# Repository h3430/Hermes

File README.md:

# Radio gateway

Work in progres...

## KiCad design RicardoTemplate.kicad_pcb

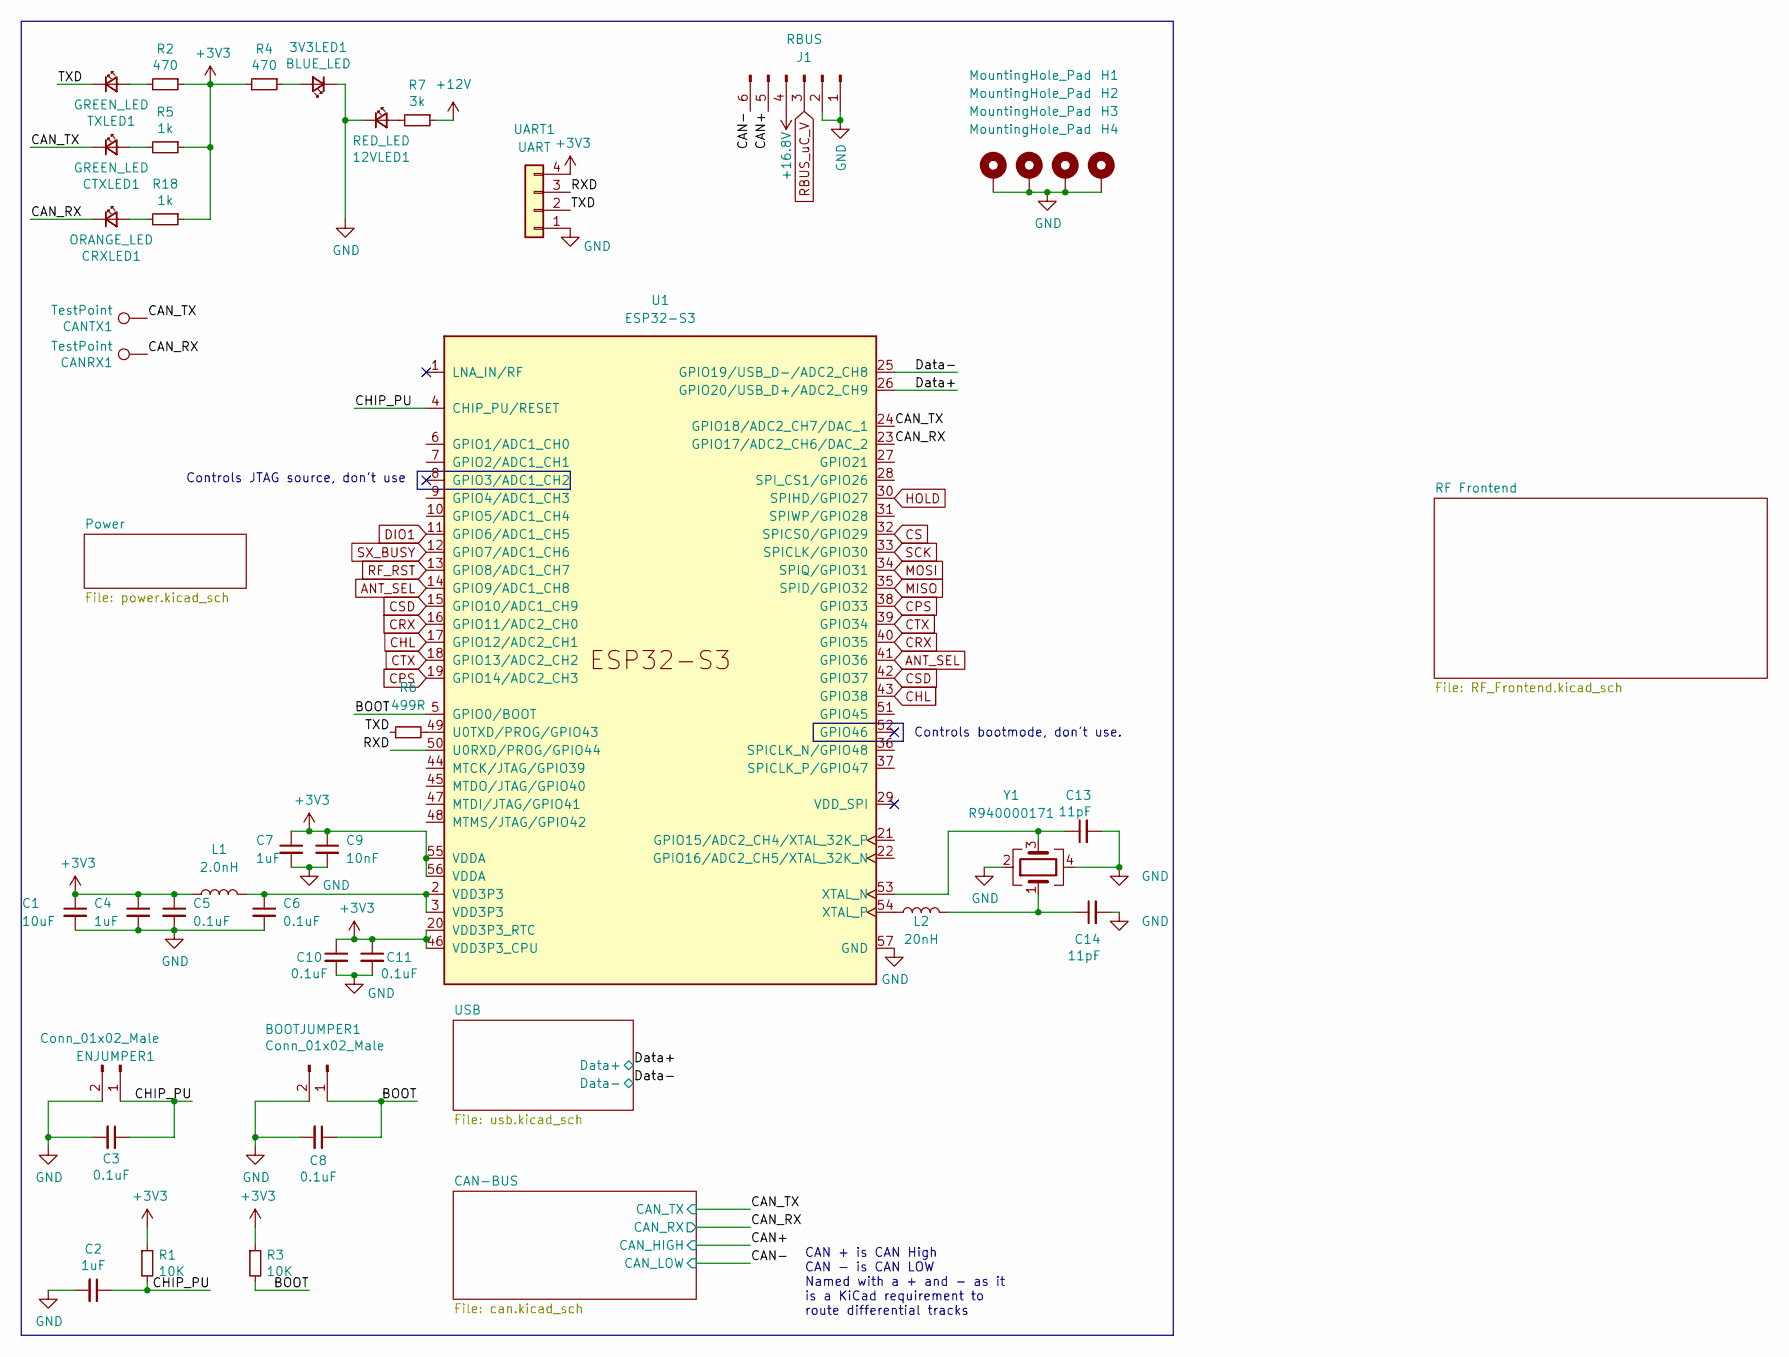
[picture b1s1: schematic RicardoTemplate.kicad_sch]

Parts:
3V3LED1: BLUE_LED; R_0402_1005Metric
12VLED1: RED_LED; R_0402_1005Metric
BOOTJUMPER1: Conn_01x02_Male; PinHeader_1x02_P2.54mm_Vertical
C1: 10uF; C_0402_1005Metric
C2, C4, C7: 1uF; C_0402_1005Metric
C3, C5, C6, C8, C10, C11: 0.1uF; C_0402_1005Metric
C9: 10nF; C_0402_1005Metric
C13, C14: 11pF; C_0402_1005Metric
CANRX1: TestPoint; TestPoint_Pad_D1.0mm
CANTX1: TestPoint; TestPoint_Pad_D1.0mm
CRXLED1: ORANGE_LED; R_0402_1005Metric
CTXLED1: GREEN_LED; R_0402_1005Metric
ENJUMPER1: Conn_01x02_Male; PinHeader_1x02_P2.54mm_Vertical
H1, H2, H3, H4: MountingHole_Pad; MountingHole_3.2mm_M3_DIN965_Pad
J1: RBUS; Molex_Mini-Fit_Jr_5566-06A_2x03_P4.20mm_Vertical
L1: 2.0nH; L_0402_1005Metric
L2: 20nH; L_0402_1005Metric
R1, R3: 10K; R_0402_1005Metric
R2, R4: 470; R_0402_1005Metric
R5, R18: 1k; R_0402_1005Metric
R6: 499R; R_0402_1005Metric
R7: 3k; R_0402_1005Metric
TXLED1: GREEN_LED; R_0402_1005Metric
U1: ESP32-S3; QFN40P700X700X90-57N
UART1: UART; PinHeader_1x04_P2.54mm_Vertical
Y1: R940000171; Crystal_SMD_2016-4Pin_2.0x1.6mm

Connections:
+3V3: C1.1, C4.1, C5.1, C7.1, C9.1, C10.1, C11.1, L1.1, R1.1, R2.1, R3.1, R4.2, R5.1, R18.1, U1.20 (VDD3P3_RTC), U1.46 (VDD3P3_CPU), U1.55 (VDDA), U1.56 (VDDA), UART1.4; also elsewhere on the board
+12V: R7.1
+16.8V: J1.4
/BOOT: BOOTJUMPER1.1, C8.1, R3.2, U1.5 (GPIO0/BOOT)
/CAN+: J1.5; also elsewhere on the board
/CAN-: J1.6; also elsewhere on the board
/CAN_RX: CANRX1.1, CRXLED1.1 (K), U1.23 (GPIO17/ADC2_CH6/DAC_2); also elsewhere on the board
/CAN_TX: CANTX1.1, CTXLED1.1 (K), U1.24 (GPIO18/ADC2_CH7/DAC_1); also elsewhere on the board
/CHIP_PU: C2.1, C3.1, ENJUMPER1.1, R1.2, U1.4 (CHIP_PU/RESET)
/Data+: U1.26 (GPIO20/USB_D+/ADC2_CH9); also elsewhere on the board
/Data-: U1.25 (GPIO19/USB_D-/ADC2_CH8); also elsewhere on the board
/RXD: U1.50 (U0RXD/PROG/GPIO44), UART1.3
/TXD: R6.1, TXLED1.1 (K), UART1.2
ANT_SEL: U1.14 (GPIO9/ADC1_CH8), U1.41 (GPIO36); also elsewhere on the board
CHL: U1.17 (GPIO12/ADC2_CH1), U1.43 (GPIO38); also elsewhere on the board
CPS: U1.19 (GPIO14/ADC2_CH3), U1.38 (GPIO33); also elsewhere on the board
CRX: U1.16 (GPIO11/ADC2_CH0), U1.40 (GPIO35); also elsewhere on the board
CS: U1.32 (SPICS0/GPIO29); also elsewhere on the board
CSD: U1.15 (GPIO10/ADC1_CH9), U1.42 (GPIO37); also elsewhere on the board
CTX: U1.18 (GPIO13/ADC2_CH2), U1.39 (GPIO34); also elsewhere on the board
DIO1: U1.11 (GPIO6/ADC1_CH5); also elsewhere on the board
GND: 3V3LED1.1 (K), 12VLED1.1 (K), BOOTJUMPER1.2, C1.2, C2.2, C3.2, C4.2, C5.2, C6.2, C7.2, C8.2, C9.2, C10.2, C11.2, C13.2, C14.2, ENJUMPER1.2, H1.1, H2.1, H3.1, H4.1, J1.1, J1.2, U1.57 (GND), UART1.1, Y1.2, Y1.4; also elsewhere on the board
HOLD: U1.30 (SPIHD/GPIO27)
MISO: U1.35 (SPID/GPIO32); also elsewhere on the board
MOSI: U1.34 (SPIQ/GPIO31); also elsewhere on the board
unnamed: 3V3LED1.2 (A), R4.1
unnamed: 12VLED1.2 (A), R7.2
unnamed: C6.1, L1.2, U1.2 (VDD3P3), U1.3 (VDD3P3)
unnamed: C14.1, L2.2, Y1.1
unnamed: CRXLED1.2 (A), R18.2
unnamed: CTXLED1.2 (A), R5.2
unnamed: R2.2, TXLED1.2 (A)
unnamed: R6.2, U1.49 (U0TXD/PROG/GPIO43)
unnamed: C13.1, U1.53 (XTAL_N), Y1.3
unnamed: L2.1, U1.54 (XTAL_P)
RBUS_uC_V: J1.3; also elsewhere on the board
RF_RST: U1.13 (GPIO8/ADC1_CH7); also elsewhere on the board
SCK: U1.33 (SPICLK/GPIO30); also elsewhere on the board
SX_BUSY: U1.12 (GPIO7/ADC1_CH6); also elsewhere on the board

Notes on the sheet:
Controls bootmode, don't use.
CAN + is CAN High CAN - is CAN LOW Named with a + and - as it is a KiCad requirement to route differential tracks
Controls JTAG source, don't use

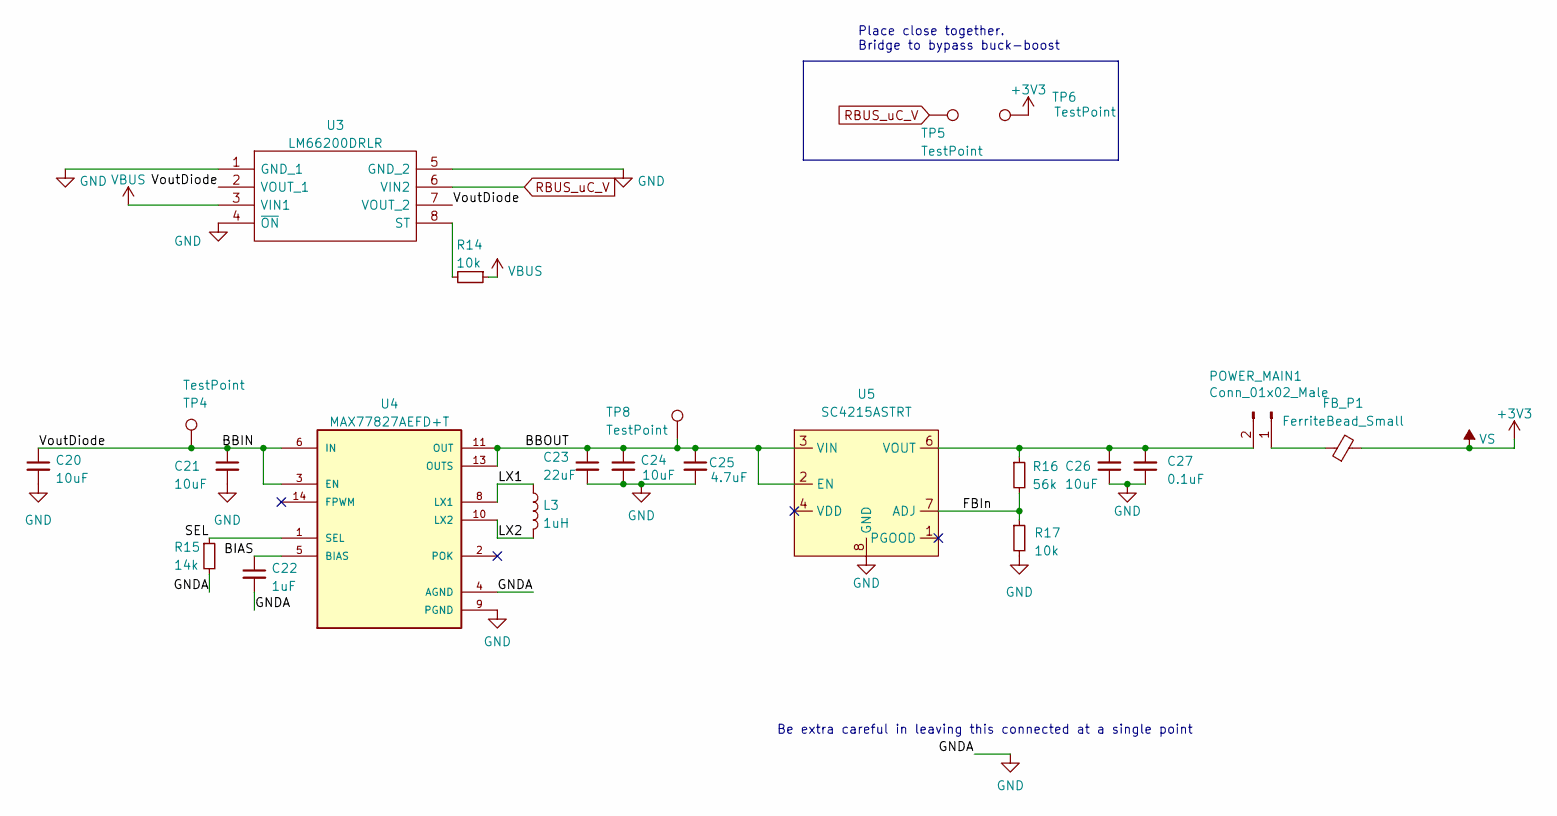
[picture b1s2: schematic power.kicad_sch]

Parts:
C20, C24, C26: 10uF; C_0402_1005Metric
C21: 10uF; C_0603_1608Metric
C22: 1uF; C_0402_1005Metric
C23: 22uF; C_0603_1608Metric
C25: 4.7uF; C_0402_1005Metric
C27: 0.1uF; C_0402_1005Metric
FB_P1: FerriteBead_Small; L_0603_1608Metric
L3: 1uH; L_0805_2012Metric
POWER_MAIN1: Conn_01x02_Male; PinHeader_1x02_P2.54mm_Vertical
R14, R17: 10k; R_0402_1005Metric
R15: 14k; R_0402_1005Metric
R16: 56k; R_0402_1005Metric
TP4, TP5, TP6, TP8: TestPoint; TestPoint_Pad_D1.5mm
U3: LM66200DRLR; SOTFL50P160X60-8N; Manufacturer_Part_Number LM66200DRLR; Mouser Part Number 595-LM66200DRLR
U4: MAX77827AEFD+T; CONV_MAX77827AEFD+T; PARTREV B
U5: SC4215ASTRT; SOIC127P599X175-9N

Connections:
+3V3: FB_P1.2, TP6.1; also elsewhere on the board
/Power/BBIN: C20.1, C21.1, TP4.1, U3.2 (VOUT_1), U3.7 (VOUT_2), U4.3 (EN), U4.6 (IN)
/Power/BBOUT: C23.1, C24.1, C25.1, TP8.1, U4.11 (OUT), U4.13 (OUTS), U5.2 (EN), U5.3 (VIN)
/Power/BIAS: C22.1, U4.5 (BIAS)
/Power/FBIn: R16.2, R17.1, U5.7 (ADJ)
/Power/LX1: L3.1, U4.8 (LX1)
/Power/LX2: L3.2, U4.10 (LX2)
/Power/SEL: R15.1, U4.1 (SEL)
GND: C20.2, C21.2, C22.2, C23.2, C24.2, C25.2, C26.1, C27.1, R15.2, R17.2, U3.1 (GND_1), U3.4 (~ON), U3.5 (GND_2), U4.4 (AGND), U4.9 (PGND), U5.8 (GND), U5.9 (GND); also elsewhere on the board
unnamed: FB_P1.1, POWER_MAIN1.1
unnamed: C26.2, C27.2, POWER_MAIN1.2, R16.1, U5.6 (VOUT)
unnamed: R14.2, U3.8 (ST)
RBUS_uC_V: TP5.1, U3.6 (VIN2); also elsewhere on the board
VBUS: R14.1, U3.3 (VIN1); also elsewhere on the board

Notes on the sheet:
Place close together. Bridge to bypass buck-boost
Be extra careful in leaving this connected at a single point

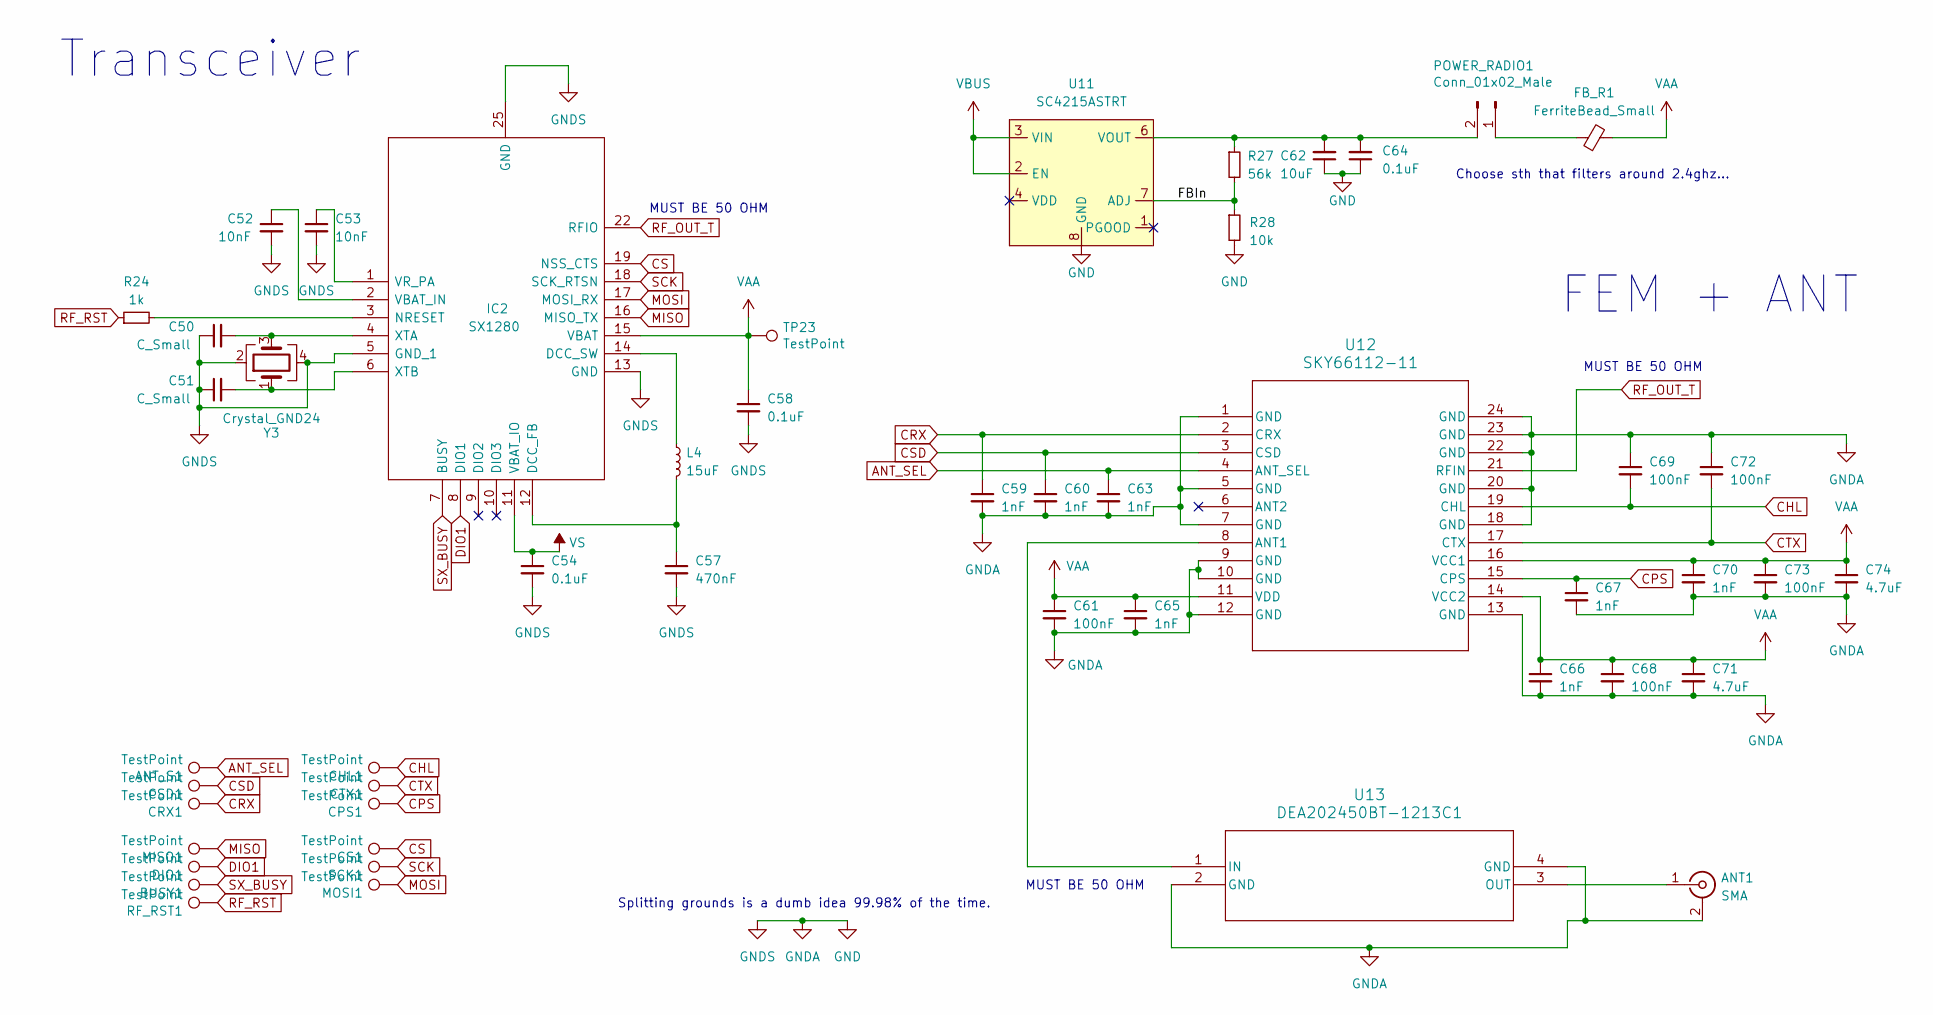
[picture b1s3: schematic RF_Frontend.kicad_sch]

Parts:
ANT1: SMA; SMA_Amphenol_901-144_Vertical
ANT_S1: TestPoint; TestPoint_Pad_D1.0mm
BUSY1: TestPoint; TestPoint_Pad_D1.0mm
C50, C51: C_Small; C_0402_1005Metric
C52, C53: 10nF; C_0402_1005Metric
C54, C58, C64: 0.1uF; C_0402_1005Metric
C57: 470nF; C_0402_1005Metric
C59, C60, C63, C65, C66, C67, C70: 1nF; C_0402_1005Metric
C61, C68, C69, C72, C73: 100nF; C_0402_1005Metric
C62: 10uF; C_0402_1005Metric
C71, C74: 4.7uF; C_0603_1608Metric
CHL1: TestPoint; TestPoint_Pad_D1.0mm
CPS1: TestPoint; TestPoint_Pad_D1.0mm
CRX1: TestPoint; TestPoint_Pad_D1.0mm
CS1: TestPoint; TestPoint_Pad_D1.0mm
CSD1: TestPoint; TestPoint_Pad_D1.0mm
CTX1: TestPoint; TestPoint_Pad_D1.0mm
DIO1: TestPoint; TestPoint_Pad_D1.0mm
FB_R1: FerriteBead_Small; L_0603_1608Metric
IC2: SX1280; QFN50P400X400X95-24N; Manufacturer_Part_Number SX1280IMLTRT; Mouser Part Number 947-SX1280IMLTRT
L4: 15uF; C_0603_1608Metric
MISO1: TestPoint; TestPoint_Pad_D1.0mm
MOSI1: TestPoint; TestPoint_Pad_D1.0mm
POWER_RADIO1: Conn_01x02_Male; PinHeader_1x02_P2.54mm_Vertical
R24: 1k; R_0402_1005Metric
R27: 56k; R_0402_1005Metric
R28: 10k; R_0402_1005Metric
RF_RST1: TestPoint; TestPoint_Pad_D1.0mm
SCK1: TestPoint; TestPoint_Pad_D1.0mm
TP23: TestPoint; TestPoint_Pad_D1.0mm
U11: SC4215ASTRT; SOIC127P599X175-9N
U12: SKY66112-11; SKY66112-11_SKY
U13: DEA202450BT-1213C1; DEA-4_2P0X1P25
Y3: Crystal_GND24; Crystal_SMD_2016-4Pin_2.0x1.6mm

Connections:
+3V3: C54.1, IC2.11 (VBAT_IO); also elsewhere on the board
/RF Frontend/FBIn: R27.2, R28.1, U11.7 (ADJ)
ANT_SEL: ANT_S1.1, C63.1, U12.4 (ANT_SEL); also elsewhere on the board
CHL: C69.2, CHL1.1, U12.19 (CHL); also elsewhere on the board
CPS: C67.1, CPS1.1, U12.15 (CPS); also elsewhere on the board
CRX: C59.1, CRX1.1, U12.2 (CRX); also elsewhere on the board
CS: CS1.1, IC2.19 (NSS_CTS); also elsewhere on the board
CSD: C60.1, CSD1.1, U12.3 (CSD); also elsewhere on the board
CTX: C72.2, CTX1.1, U12.17 (CTX); also elsewhere on the board
DIO1: DIO1.1, IC2.8 (DIO1); also elsewhere on the board
GND: ANT1.2 (Ext), C50.1, C51.1, C52.2, C53.2, C54.2, C57.2, C58.2, C59.2, C60.2, C61.2, C62.1, C63.2, C64.1, C65.2, C66.2, C67.2, C68.2, C69.1, C70.2, C71.2, C72.1, C73.2, C74.2, IC2.5 (GND_1), IC2.13 (GND), IC2.20 (GND), IC2.21 (GND), IC2.23 (GND), IC2.24 (GND), IC2.25 (GND), R28.2, U11.8 (GND), U11.9 (GND), U12.1 (GND), U12.5 (GND), U12.7 (GND), U12.9 (GND), U12.10 (GND), U12.12 (GND), U12.13 (GND), U12.18 (GND), U12.20 (GND), U12.22 (GND), U12.23 (GND), U12.24 (GND), U13.2 (GND), U13.4 (GND), Y3.2, Y3.4; also elsewhere on the board
MISO: IC2.16 (MISO_TX), MISO1.1; also elsewhere on the board
MOSI: IC2.17 (MOSI_RX), MOSI1.1; also elsewhere on the board
unnamed: ANT1.1 (In), U13.3 (OUT)
unnamed: C57.1, IC2.12 (DCC_FB), L4.2
unnamed: IC2.14 (DCC_SW), L4.1
unnamed: IC2.3 (NRESET), R24.2
unnamed: C52.1, IC2.2 (VBAT_IN)
unnamed: C53.1, IC2.1 (VR_PA)
unnamed: C50.2, IC2.4 (XTA), Y3.3
unnamed: C51.2, IC2.6 (XTB), Y3.1
unnamed: FB_R1.1, POWER_RADIO1.1
unnamed: C62.2, C64.2, POWER_RADIO1.2, R27.1, U11.6 (VOUT)
unnamed: U12.8 (ANT1), U13.1 (IN)
RF_OUT_T: IC2.22 (RFIO), U12.21 (RFIN)
RF_RST: R24.1, RF_RST1.1; also elsewhere on the board
SCK: IC2.18 (SCK_RTSN), SCK1.1; also elsewhere on the board
SX_BUSY: BUSY1.1, IC2.7 (BUSY); also elsewhere on the board
VAA: C58.1, C61.1, C65.1, C66.1, C68.1, C70.1, C71.1, C73.1, C74.1, FB_R1.2, IC2.15 (VBAT), TP23.1, U12.11 (VDD), U12.14 (VCC2), U12.16 (VCC1)
VBUS: U11.2 (EN), U11.3 (VIN); also elsewhere on the board

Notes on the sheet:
FEM + ANT
MUST BE 50 OHM
Transceiver
Choose sth that filters around 2.4ghz...
Splitting grounds is a dumb idea 99.98% of the time.

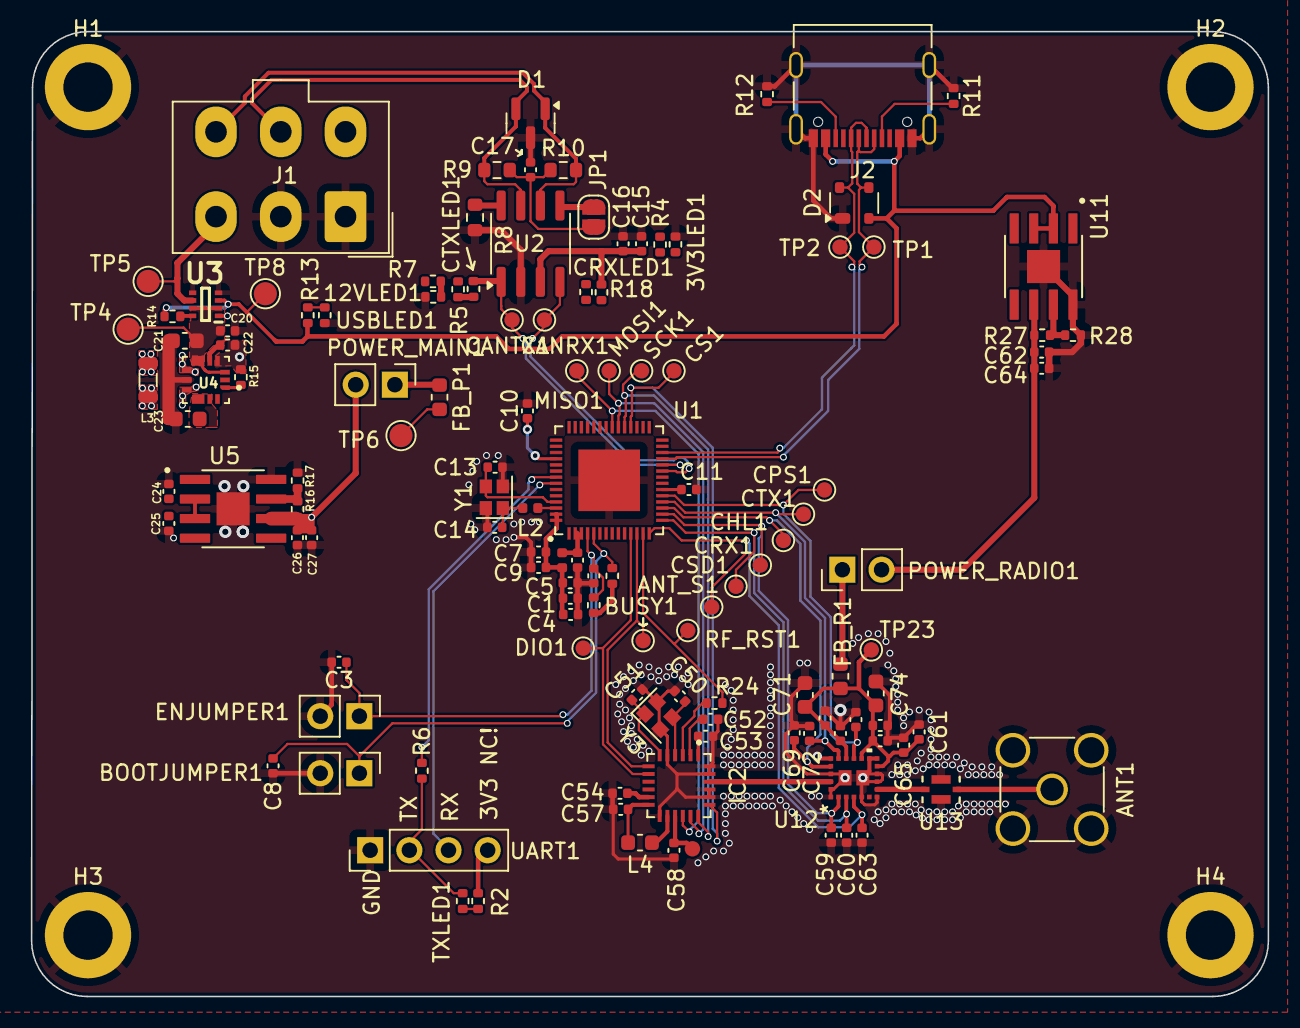
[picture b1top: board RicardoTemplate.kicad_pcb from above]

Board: 4 copper layers, 80.2 x 62.6 mm, 128 parts (0 on the bottom side), 67 nets.

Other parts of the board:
C15: 100nF; C_0402_1005Metric
C16: 10uF; C_0402_1005Metric
C17: 47nF; C_0402_1005Metric
D1: SM712_SOT23; SOT-23
D2: SP0503BAHT; SOT-143
J2: USB_C_Receptacle_USB2.0; USB_C_Receptacle_Palconn_UTC16-G
JP1: TermJP; SolderJumper-2_P1.3mm_Open_RoundedPad1.0x1.5mm
R8: 0; R_0603_1608Metric
R9, R10: 60; R_0603_1608Metric
R11, R12, R13: 5.1k; R_0402_1005Metric
TP1, TP2: TestPoint; TestPoint_Pad_D1.0mm
U2: SN65HVD230; SOIC-8_3.9x4.9mm_P1.27mm
USBLED1: WHITE_LED; R_0402_1005Metric

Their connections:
+3V3: C15.1, C16.1, U2.3 (VCC); also elsewhere on the board
/CAN+: D1.2 (A2), R9.1, U2.7 (CANH); also elsewhere on the board
/CAN-: D1.1 (A1), R10.2, U2.6 (CANL); also elsewhere on the board
/CAN-BUS/Vref: JP1.1 (A), U2.5 (Vref)
/CAN_RX: U2.4 (R); also elsewhere on the board
/CAN_TX: U2.1 (D); also elsewhere on the board
/Data+: D2.4 (K), J2.A6 (D+), J2.B6 (D+), TP2.1; also elsewhere on the board
/Data-: D2.3 (K), J2.A7 (D-), J2.B7 (D-), TP1.1; also elsewhere on the board
GND: C15.2, C16.2, C17.2, D1.3 (common), D2.1 (A), J2.A1 (GND), J2.A12 (GND), J2.B1 (GND), J2.B12 (GND), J2.S1 (SHIELD), R8.2, R11.2, R12.1, U2.2 (GND), USBLED1.1 (K); also elsewhere on the board
unnamed: J2.A5 (CC1), R11.1
unnamed: J2.B5 (CC2), R12.2
unnamed: C17.1, JP1.2 (B), R9.2, R10.1
unnamed: R8.1, U2.8 (Rs)
unnamed: R13.2, USBLED1.2 (A)
VBUS: D2.2 (K), J2.A4 (VBUS), J2.A9 (VBUS), J2.B4 (VBUS), J2.B9 (VBUS), R13.1; also elsewhere on the board

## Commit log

2024-11-06 Initial Design
    Weeeeeeeee
2024-11-22 Alpha revision
    Bulk of routing, layout and etc... is done, design needs to be refined, via stitched and reviewed.
2024-11-24 Minor improvements
